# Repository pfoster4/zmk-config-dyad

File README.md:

# Dyad Keyboard

*A compact, wireless, split ergonomic keyboard designed with travel and simplicity in mind.*

## Features
- **Wireless w/ Dongle** powered by ZMK firmware for work computers without bluetooth
- **34-key split layout** with 3x5 columnn staggered keys and two thumb keys per half
- **Super long battery life estimated at 9-12 months** with 850 mAh batteries in each half as peripherals 
- **Simple and clean look** with components hidden out of sight and no unnecessary features
- **Reed switch + magnets** for travel convenience 
- **Ambients Silent Choc switches and LDSA low-profile keycaps**

## Table of Contents
- [Why does this Exist?](#why-does-this-exist?)
- [Keymap](#keymap)
- [Parts List](#parts-list)
- [Build Guide](#build-guide)
- [Helpful Resources](#helpful-resources)

## Why does this Exist?
I designed Dyad because I couldn't find another keyboard that had exactly what I needed, without all the extra stuff I didn't. Also, let's be honest–if you're here, you either have the same sickness as me, or a morbid (and very niche) sense of curiosity. 

I travel a lot for work, and have been using a Piantor keyboard for the last year or so. Unfortunately, I plugged it in with the TRRS cable only partially inserted and fried one of the microcontrollers. I decided to take the opportunity as an excuse to design my own board from scratch. 

Wires are cumbersome and can be annoying. Obviously this thing needs to be wireless. I move around between computers at work, and none of them have built in bluetooth. Using a dongle solves this, making both halves peripherals instead of host devices. This balances power usage and extends battery life. I found the Seeed Studio XIAO nRF52840 microcontroller to be a great option for this. It's super small, has BLE functionality, and is relatively cheap. I found a small USB-C to USB-A adapter that fit inside a recess I put in the case, so everything packs together nicely. 

I wanted to maximize my battery life. I like simple keyboards. Extra features like OLEDs are cool, but they still draw power and reduce battery life. Dyad is intentionally very simple in its features, which helps strive towards a keyboard that rarely needs charging. 

I didn't like having an exposed microcontroller on the front of the board. It's very easy to short the pins with a drop of coffee (oops), and the microcontoller takes up precious real estate for what could otherwise be a smaller profile. Instead of mounting the microcontroller on top like most builds, I soldered it directly to the back of the PCB–no headers, no cutouts, no exposed pins. The XIAO board does require diodes at this key count, but there's still plenty of room to fit a 850 mAh battery, and get a subtle but noticable five degree tenting angle for better wrist ergonomics. 

Finally, I like the idea of magnets holding the two keyboard halves together like a few other board designers have done. I wanted to take it a step further and introduce reed switches in a normally closed configuration to the power circuits. This makes it impossible to forget to leave the board on or accidentally send keypresses when traveling, since the circuit will switch open whenever the two keyboard halves are magnetically latched together. Is this a bit gimmicky? Sure. But is it useful? I think so! If you'd prefer, you can bridge the dedicated solder pads instead of using a reed switch, and just rely on the normal slider switch. The magnetic attachment and automatic power management make Dyad especially convenient for travel–no worrying about whether it's on or off. 

The result? A wireless, travel-friendly, durable split keyboard that stays charged for ages and looks pretty good doing it. 

## Keymap
This keymap is a modified version of [Miryoku](https://github.com/manna-harbour/miryoku), a layered layout architecture intended for 3x5 keyboard halves with three thumb keys. We need to find a way to replicate the third thumb key Dyad only has two thumb keys. This is accomplished by using key combos. Tapping or holding both thumb keys on one half will perform the same behavior as the missing third thumb key. Additional combos are added for convenience.

This keymap has six non-default layers to access full functionality of the keyboard: a number layer, symbol layer, function key layer, mouse control layer, navigation layer, and media control layer. Each layer is accessed by holding down the thumb keys as shown in the keymap diagram below.

## Parts List
Many of these components have acceptable alternatives. Be sure to double check the PCB footprint requirements before deviating.

| Component | Description | Quantity |
|-----------|-------------|----------|
| PCBs | [Custom-designed Dyad PCBs](https://github.com/dyad-keeb/zmk-config-dyad/tree/main/pcb/zip%20files) | 1x of each half |
| Microcontrollers | [Seeed Studio XIAO nRF52840](https://www.mouser.com/ProductDetail/Seeed-Studio/102010448?qs=Znm5pLBrcAJ5g%252BWAkitg4w%3D%3D&countryCode=US&currencyCode=USD) | 2x (BT) or 3x (Dongle) |
| Key Switches | [Choc Switches (Ambients Silent Twilights)](https://lowprokb.ca/products/ambients-silent-choc-switches) | 34x |
| Keycaps | [Low Profile LSDA Caps (1u blanks)](https://lowprokb.ca/collections/keycaps/products/ldsa-low-profile-blank-keycaps) | 34x |
| Diodes | [SMD Diodes](https://www.mouser.com/ProductDetail/Micro-Commercial-Components-MCC/MMSZ5246B-TP?qs=ZNK0BnemlqEr9Va1g49r5g%3D%3D&countryCode=US&currencyCode=USD) | 34x |
| Power Switches | [SLW-66527511-SMT-TR](https://www.mouser.com/ProductDetail/Same-Sky/SLW-66527511-SMT-TR?qs=1Kr7Jg1SGW%252BCp04CqrZlUg%3D%3D&countryCode=US&currencyCode=USD) | 2x |
| Batteries | [ASR00036 850 mAh](https://www.mouser.com/ProductDetail/TinyCircuits/ASR00036?qs=byeeYqUIh0Mizxtsp6GM5A%3D%3D) | 2x |
| Battery Connectors | [SM02B-SRSS-TB](https://www.mouser.com/ProductDetail/JST-Commercial/SM02B-SRSS-TBLFSN?qs=cdbOS8ANM9BWPfwllEYjZw%3D%3D) | 2x |
| Reset Buttons | [B3U-1000P-B](https://www.mouser.com/ProductDetail/Omron-Electronics/B3U-1000P-B?qs=AO7BQMcsEu6QxhKppRpaJA%3D%3D) | 2x |
| Reed Switches (optional) | [MK24-B-2-OE](https://www.mouser.com/ProductDetail/MEDER-electronic/MK24-B-2-OE?qs=E8j%2FIcuE3oXcUsXW7SbUjw%3D%3D&countryCode=US&currencyCode=USD) | 2x |
| Magnets | [Magnets, 10mm x 5mm x 2mm](https://www.amazon.com/dp/B0B6VKY7Y2?ref_=ppx_hzsearch_conn_dt_b_fed_asin_title_4) | 10x |
| Press-Fit Nuts | [2-56 Thread for 0.147" Dia Hole](https://www.mcmaster.com/94648A310/) | 4x |
| Spring Pins | [1/16" Dia x 3/16" Long](https://www.mcmaster.com/98296A015/) | 8x |
| Screws | [2-56 Thread x 1/8" Long](https://www.mcmaster.com/92949A174/) | 4x |
| Grippy Bumpers | [1/4" Dia x 1/16" Thick](https://www.amazon.com/dp/B07R17T68B?ref_=ppx_hzsearch_conn_dt_b_fed_asin_title_2) | 10x |
| Dongle Adapter | [USB-C male to USB-A male](https://www.amazon.com/dp/B0CFLWC8G1?ref=ppx_yo2ov_dt_b_fed_asin_title) | 1x |
| 3D Printed Cases | [Case files](https://github.com/dyad-keeb/zmk-config-dyad/tree/main/case) and [my preferred filament](https://www.amazon.com/dp/B08142W8XV?ref=ppx_yo2ov_dt_b_fed_asin_title) | ~60g |

## Build Guide
Read the Dyad build guide [here](https://github.com/dyad-keeb/zmk-config-dyad/tree/main/build-guide.md).

## Helpful Resources
- [Dyad CAD files](https://cad.onshape.com/documents/7f572f5029fef8eead929f6f/w/3338eb399b68b4bec0be7aa8/e/8d690b2dc0af4d791bdff9ef?renderMode=1&uiState=67ba591a8b0f840d79069d80)
- [ZMK Keymap Editor](https://nickcoutsos.github.io/keymap-editor/)
- [ZMK Docs](https://zmk.dev/docs)
- [Keyboard PCB Design Guide](https://github.com/ruiqimao/keyboard-pcb-guide)
- [FlatFootFox's Ergogen and KiCAD Guide](https://flatfootfox.com/ergogen-introduction/)
- [DIY Split Keyboard Guide](https://thomasbaart.nl/build-guide/)
- [Ergonomic Keyboard Community](https://www.reddit.com/r/ErgoMechKeyboards/)

---

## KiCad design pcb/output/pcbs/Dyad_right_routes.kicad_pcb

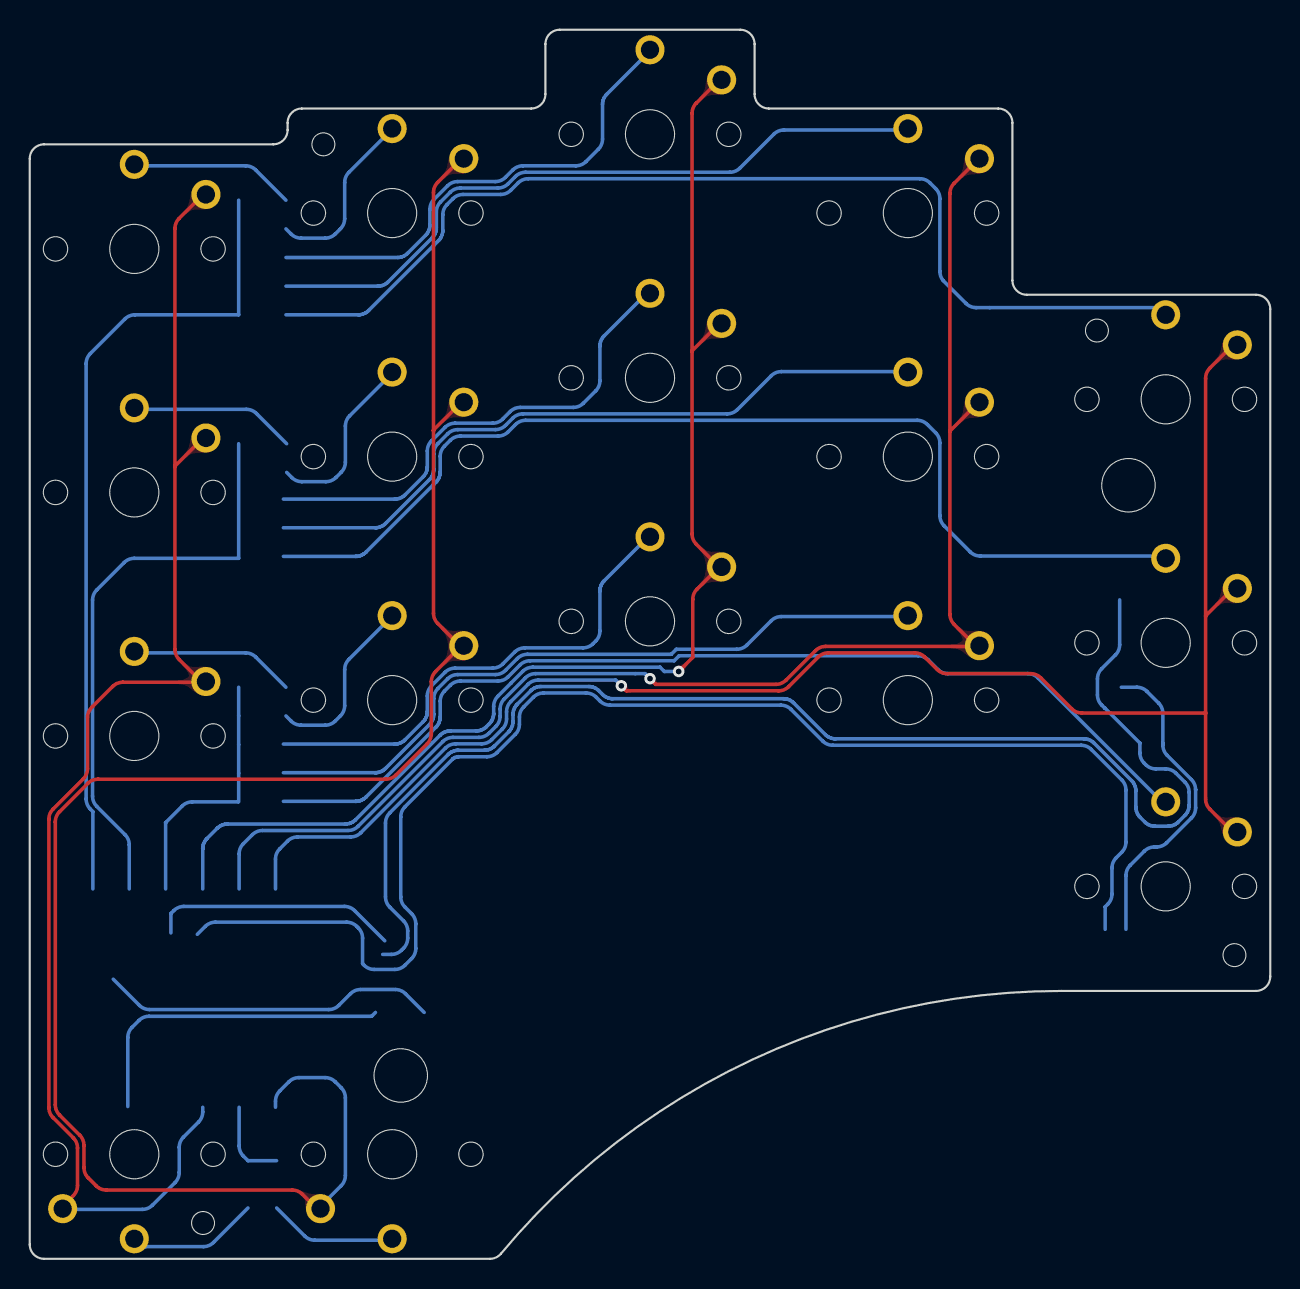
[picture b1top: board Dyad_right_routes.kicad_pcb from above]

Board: 2 copper layers, 86.6 x 85.8 mm, 19 parts (0 on the bottom side), 6 nets.

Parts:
S1, S2, S3, S4, S5, S6, S7, S8, S9, S10, S11, S12, S13, S14, S15, S16, S17: PG1350
S20: pcm12
S21: header

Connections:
BATP: S20.1, S21.BAT+
C0: S13.1, S14.1, S15.1, S16.1, S21.D10
C1: S10.1, S11.1, S12.1, S17.1, S21.D8
C2v: S7.1, S8.1, S9.1, S21.D3
C3v: S4.1, S5.1, S6.1, S21.D4
C4v: S1.1, S2.1, S3.1, S21.D5

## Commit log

2025-02-23 initial zmk commit
2025-02-23 added photos
2025-02-23 Update README.md with keycap
2025-02-23 Update README.md with stowed image
2025-02-23 F5 combo move
2025-02-24 added pcb zip files and via comment
2025-02-24 added case stl files
2025-02-24 started to write out build guide page
2025-02-24 minor readme and build guide tweaks
2025-02-24 Update README.md with why this exists section.
2025-02-25 Update README.md screw count
2025-02-25 Edit license.md
2025-02-26 Contributed a few sections to the build-guide.md
2025-02-27 Update build-guide.md kicad image
2025-02-27 Update README.md ToC link
2025-02-27 Update build-guide.md ToC links
2025-03-02 prep for travel case addition
2025-03-03 added travel case photos
2025-04-04 Rename dyad_peripheral_left.conf to dyad_central_left.conf
2025-04-04 Rename dyad_peripheral_left.overlay to dyad_central_left.overlay
2025-04-07 Update dyad.keymap
    Updated Tap time from 120 to 500
2025-04-09 Update dyad.conf
    added CONFIG_ZMK_POINTING=y
2025-04-09 Update dyad.keymap
    Modified hold keys on Layer 0 and added nav keys to Layer 1
2025-04-11 Update dyad.keymap
    A lot of updates
